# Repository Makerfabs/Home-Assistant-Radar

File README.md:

# Makerfabs Home Assistant Radar

## Intruduce

[Product Link]()

[Wiki Link]()

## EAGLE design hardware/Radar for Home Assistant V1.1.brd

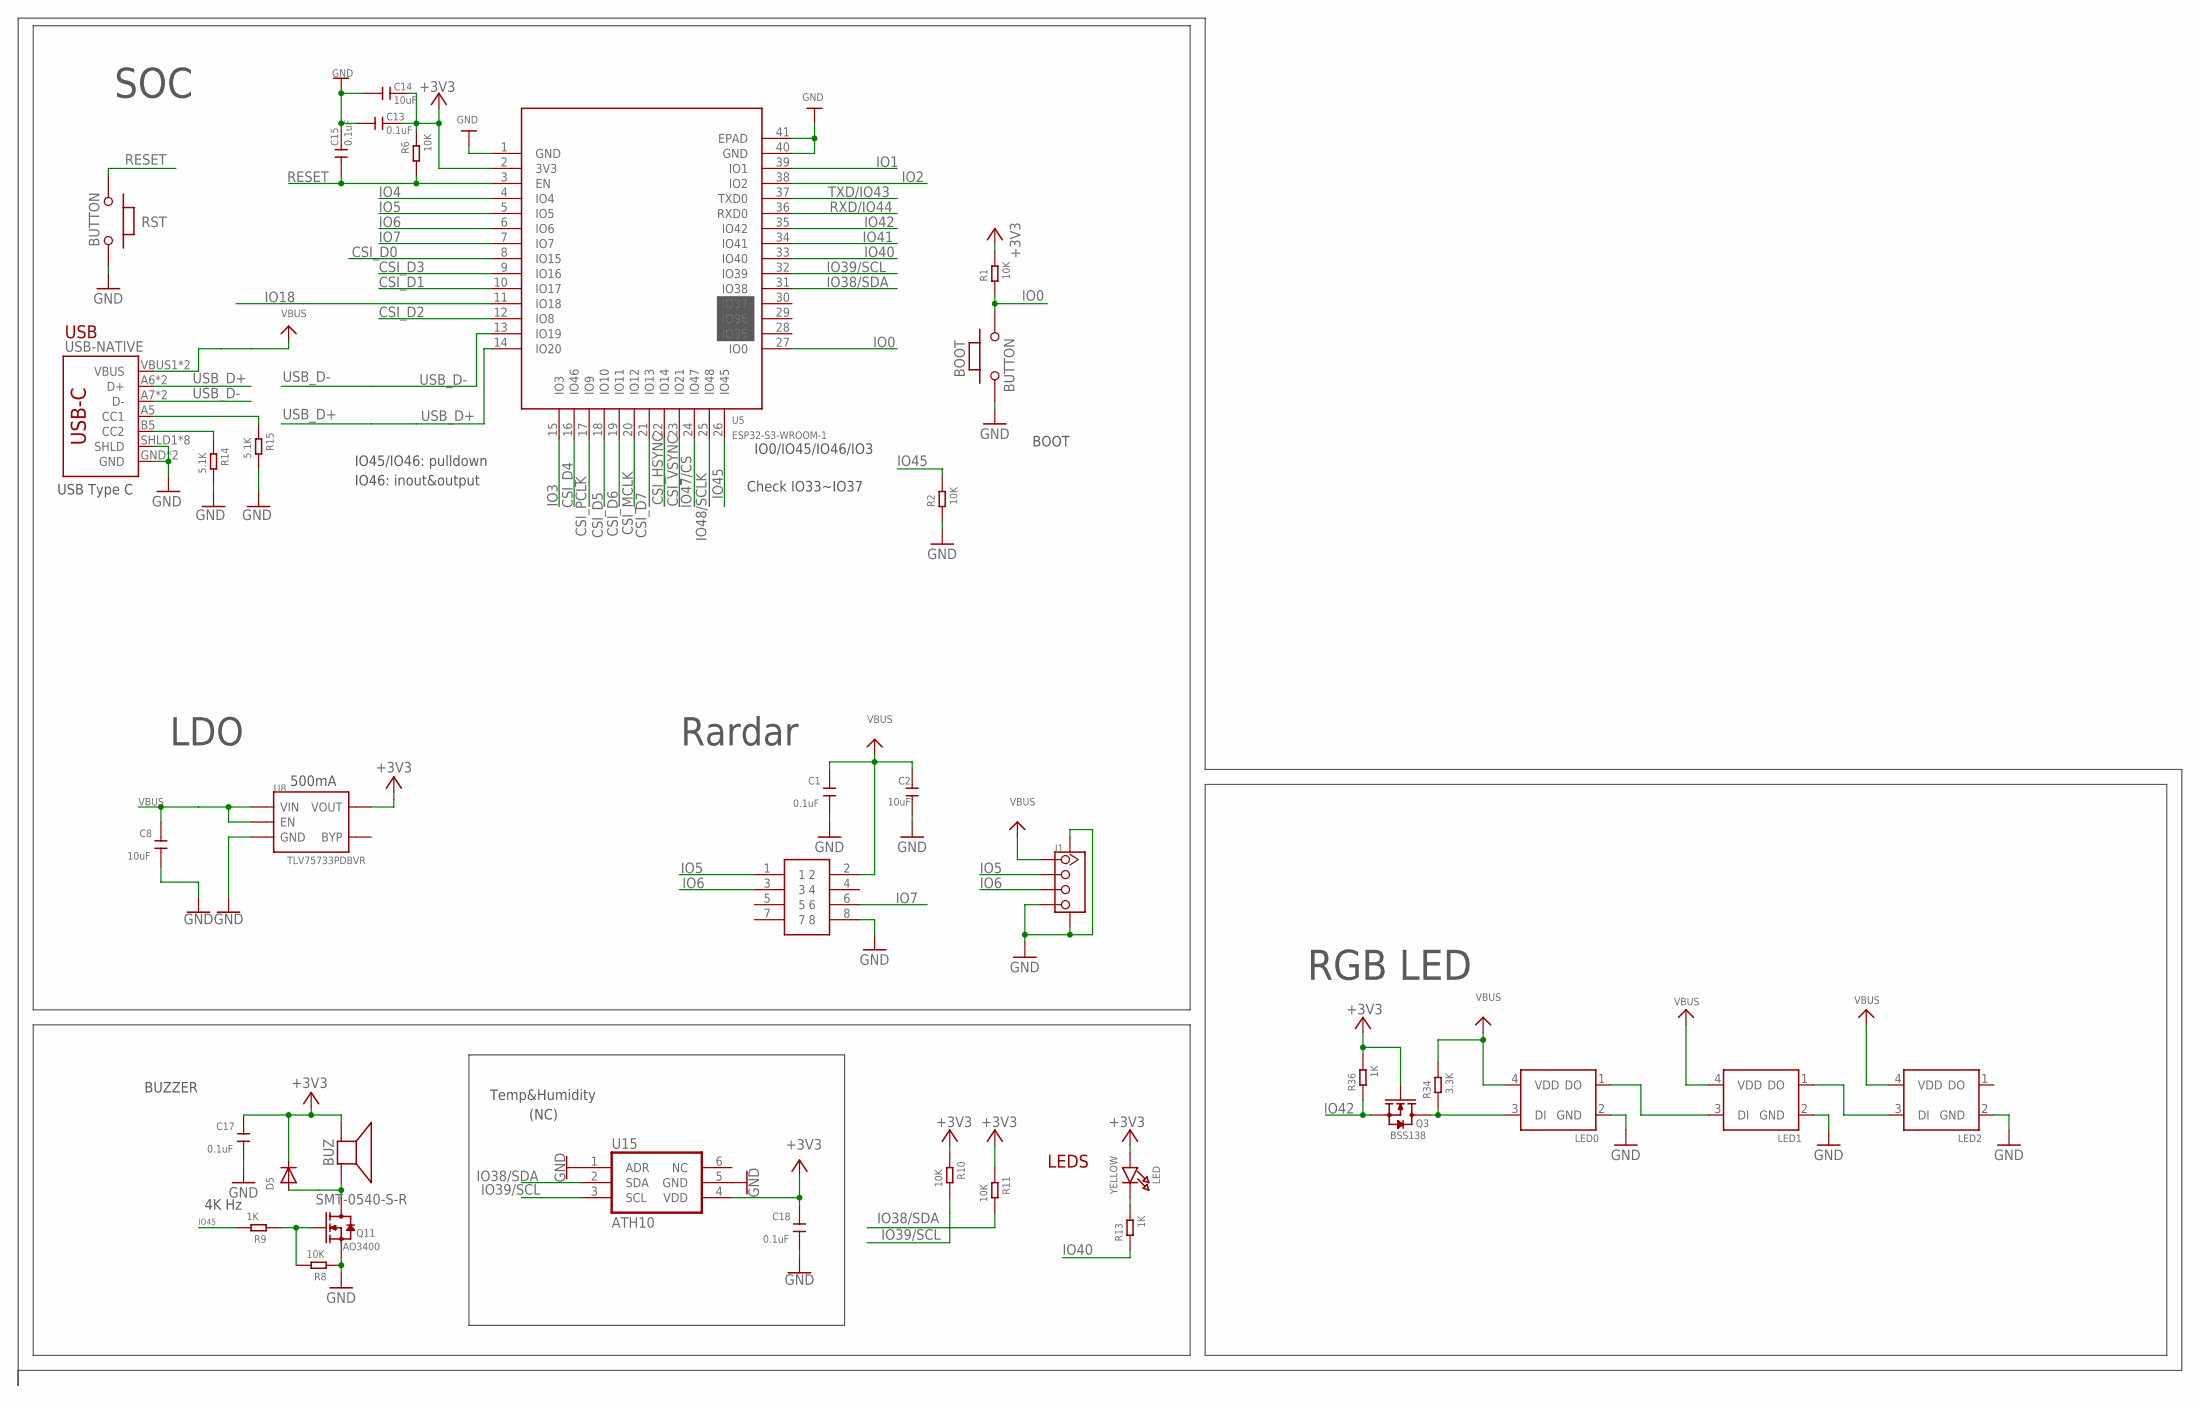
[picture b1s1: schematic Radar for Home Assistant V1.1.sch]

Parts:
BOOT: BUTTON; 157SW
BUZ: SMT-0540-S-R
C1, C13, C15, C17, C18: 0.1uF; DISCRETE_C0402
C2, C8, C14: 10uF; DISCRETE_C0402
D5: DIODESOD-323F; SOD-323F
J1: TWIG-4P-2.0-SMD-FEMALE-REINFORCE; 4P-SMD-2.0-90D-W/O-BUCKLE
J3: CON2X4-2.0MM-THD
LED: YELLOW; CHIPLED_0805_NOOUTLINE
LED0, LED1, LED2: WS2812B-2020
Q3: BSS138; SOT23@1
Q11: AO3400; SOT23@1
R1, R2, R6, R8, R10, R11: 10K; DISCRETE_R0402
R9, R13, R36: 1K; DISCRETE_R0402
R14, R15: 5.1K; DISCRETE_R0402
R34: 3.3K; DISCRETE_R0402
RST: BUTTON; 157SW
U5: ESP32-S3-WROOM-1
U8: TLV75733PDBVR; SOT23-5
U15: ATH10; AHT10
USB-NATIVE: USB_C5; USB-C-16P-5

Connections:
+3V3: BUZ.+ (-), C13.1, C14.1, C17.2, C18.2, D5.C, LED.A, Q3.1 (G), R1.2, R6.2, R10.1, R11.1, R36.2, U5.2 (3V3), U8.5 (VOUT), U15.4 (VDD)
CSI_D0: U5.8 (IO15)
CSI_D1: U5.10 (IO17)
CSI_D2: U5.12 (IO8)
CSI_D3: U5.9 (IO16)
CSI_D4: U5.16 (IO46)
CSI_D5: U5.18 (IO10)
CSI_D6: U5.19 (IO11)
CSI_D7: U5.21 (IO13)
CSI_HSYNC: U5.22 (IO14)
CSI_MCLK: U5.20 (IO12)
CSI_PCLK: U5.17 (IO9)
CSI_VSYNC: U5.23 (IO21)
GND: BOOT.1, C1.1, C2.1, C8.1, C13.2, C14.2, C15.1, C17.1, C18.1, J1.4, J1.SS1, J1.SS2, J3.8, LED0.2 (GND), LED1.2 (GND), LED2.2 (GND), Q11.2 (S), R2.1, R8.1, R14.2, R15.2, RST.1, U5.1 (GND), U5.40 (GND), U5.41 (EPAD), U8.2 (GND), U15.1 (ADR), U15.5 (GND), USB-NATIVE.GND, USB-NATIVE.GND2 (GND), USB-NATIVE.SHLD1 (SHLD), USB-NATIVE.SHLD2 (SHLD), USB-NATIVE.SHLD3 (SHLD), USB-NATIVE.SHLD4 (SHLD), USB-NATIVE.SHLD5 (SHLD), USB-NATIVE.SHLD6 (SHLD), USB-NATIVE.SHLD7 (SHLD), USB-NATIVE.SHLD8 (SHLD)
IO0: BOOT.2, R1.1, U5.27 (IO0)
IO1: U5.39 (IO1)
IO2: U5.38 (IO2)
IO3: U5.15 (IO3)
IO4: U5.4 (IO4)
IO5: J1.2, J3.1, U5.5 (IO5)
IO6: J1.3, J3.3, U5.6 (IO6)
IO7: J3.6, U5.7 (IO7)
IO18: U5.11 (IO18)
IO38/SDA: R11.2, U5.31 (IO38), U15.2 (SDA)
IO39/SCL: R10.2, U5.32 (IO39), U15.3 (SCL)
IO40: R13.1, U5.33 (IO40)
IO41: U5.34 (IO41)
IO42: Q3.2 (S), R36.1, U5.35 (IO42)
IO45: R2.2, R9.2, U5.26 (IO45)
IO47/CS: U5.24 (IO47)
IO48/SCLK: U5.25 (IO48)
M-1: BUZ.- (+), D5.A, Q11.3 (D)
unnamed: LED1.1 (DO), LED2.3 (DI)
unnamed: LED0.1 (DO), LED1.3 (DI)
unnamed: LED.C, R13.2
unnamed: LED0.3 (DI), Q3.3 (D), R34.1
unnamed: Q11.1 (G), R8.2, R9.1
unnamed: R15.1, USB-NATIVE.A5 (CC1)
unnamed: R14.1, USB-NATIVE.B5 (CC2)
RESET: C15.2, R6.1, RST.2, U5.3 (EN)
RXD/IO44: U5.36 (RXD0)
TXD/IO43: U5.37 (TXD0)
USB_D+: U5.14 (IO20), USB-NATIVE.A6 (D+), USB-NATIVE.B6 (D+)
USB_D-: U5.13 (IO19), USB-NATIVE.A7 (D-), USB-NATIVE.B7 (D-)
VBUS: C1.2, C2.2, C8.2, J1.1, J3.2, LED0.4 (VDD), LED1.4 (VDD), LED2.4 (VDD), R34.2, U8.1 (VIN), U8.3 (EN), USB-NATIVE.VBUS1 (VBUS), USB-NATIVE.VBUS2 (VBUS)

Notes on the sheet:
500mA
LDO
LEDS
BOOT
IO45/IO46: pulldown
IO46: inout&output
USB
USB Type C
IO0/IO45/IO46/IO3
Check IO33~IO37
SOC
BUZZER
4K Hz
Temp&Humidity
RGB LED
Rardar
(NC)

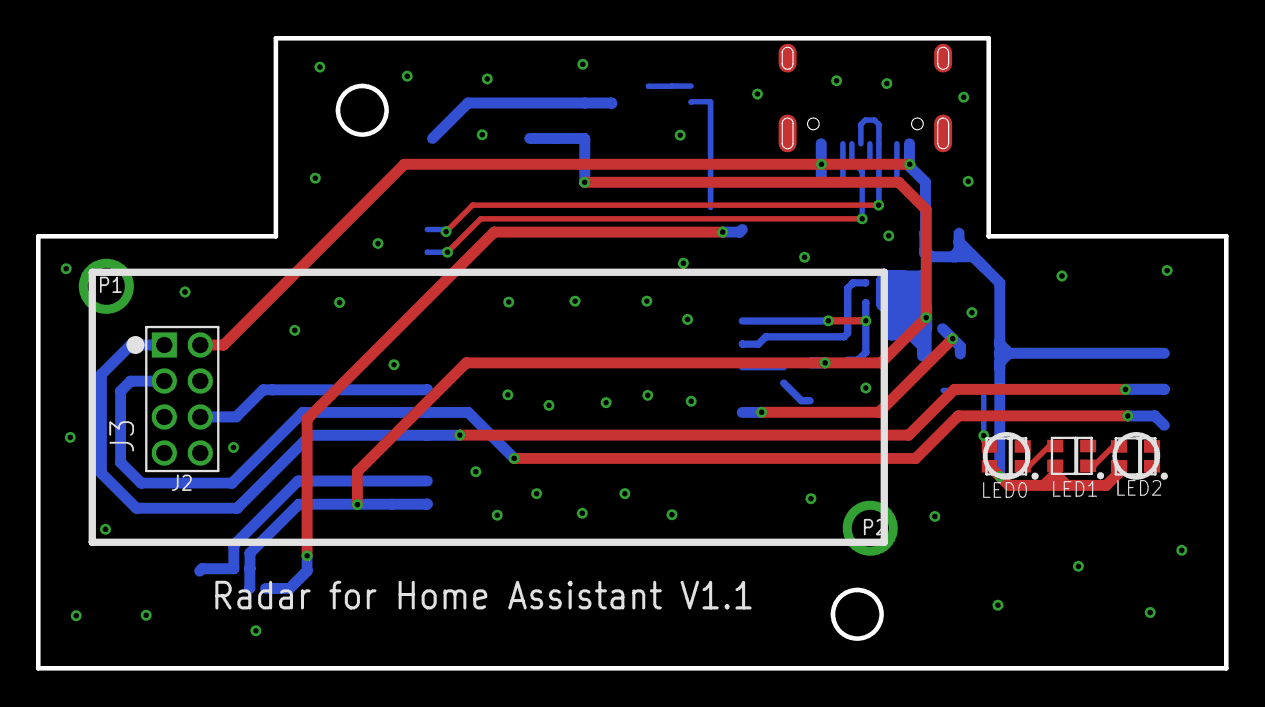
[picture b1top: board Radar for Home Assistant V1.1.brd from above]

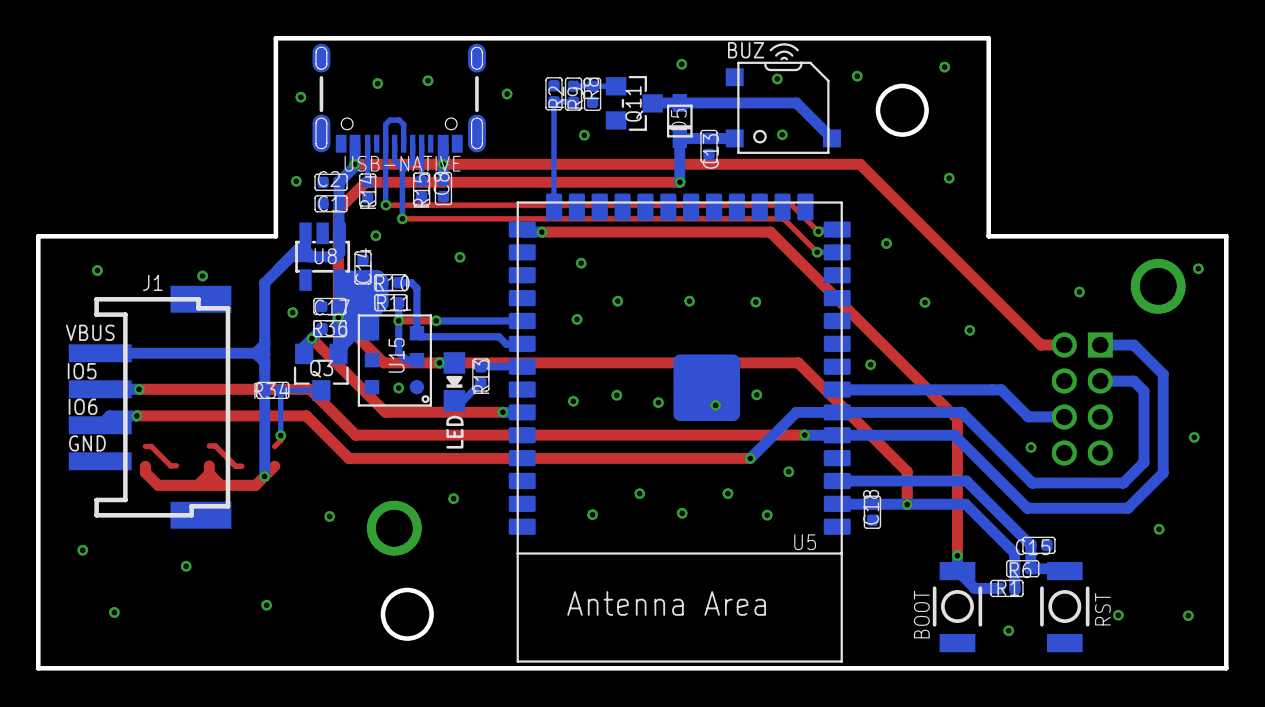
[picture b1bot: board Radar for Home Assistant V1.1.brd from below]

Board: 2 copper layers, 66.0 x 35.0 mm, 36 parts (32 on the bottom side), 23 nets.

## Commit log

2026-01-29 add hardware&yaml
2026-01-31 update yaml
2026-02-02 add ld2450 office ref files

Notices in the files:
parts and their libraries:
microbuilder: This work is placed in the public domain, and may be freely used for commercial and non-commercial work with the following conditions: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
SparkFun-PowerSymbols: Licensing: Creative Commons ShareAlike 4.0 International - https://creativecommons.org/licenses/by-sa/4.0
